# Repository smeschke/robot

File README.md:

Robot Platform 🛠️

Modular ESP32-based robot platform for outdoor navigation, motor control, and sensor integration.

This is a human-scale, differential-drive utility robot designed to move comfortably through real-world, ADA-compliant spaces at walking speed.

I chose 10-inch pneumatic tires so the robot can handle sidewalks, ramps, and grass reliably without suspension. The motors, gearboxes, and battery come from ride-on toys—they're inexpensive, readily available, and deliver excellent torque at low speeds.

The robot is controlled by an ESP32. The ESP32 uses ESPNOW to communicate with a manual joystick, or a computer. This allows the user to switch from 'auto' to 'manual' without touching any cords.

🔧 Technical Snapshot

The robot uses 550-type brushed DC motors with 100:1 reduction gearboxes driving 10-inch pneumatic wheels. It's powered by 12-volt, 7 amp-hour sealed lead-acid battery(s). Motor control is handled by BTS7960 H-bridge motor drivers.

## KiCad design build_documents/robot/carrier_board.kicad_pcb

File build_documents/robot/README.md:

# The Robot 🤖

Human-scale differential-drive utility robot built from ride-on toy parts: 550-type brushed motors with 100:1 gearboxes on 10-inch pneumatic wheels, powered by 12 V 7 Ah sealed lead-acid, driven by BTS7960 H-bridges. Ride-on toy drivetrains are cheap, everywhere, and geared for exactly this job — high torque at walking speed. The pneumatic tires handle sidewalks, ramps, and grass without any suspension, and it'll tow a cart.

## Architecture

There's no single robot brain — it's two independent ESP32s, each listening on ESP-NOW:

- **Motor board** ([`firmware/skidsteer_espnow.ino`](../../firmware/skidsteer_espnow.ino)) — receives the drive stream, does the skid-steer mixing, runs four BTS7960 channels.
- **Relay board** ([`firmware/relay_receiver.ino`](../../firmware/relay_receiver.ino)) — receives light events, drives two relays (left/right lights) for latched headlights and 2-second momentary turn signals.

Receivers tell packets apart purely by length (12-byte drive, 5-byte light event), so both boards can share the airwaves without a header byte or any routing. Anything that speaks the protocol can drive it — the single stick, the dual stick, or a computer through a reflashed controller — and switching between manual and auto control never involves touching a cord.

## Drive behavior

The motor board turns the joystick stream into arcade-mixed skid steer (throttle ± turn), with two safety behaviors worth knowing:

- **Fail-safe stop.** If no drive packet arrives for 300 ms, targets go to zero. The controller streams every 5 ms, so this only trips when the link is actually gone.
- **Ramping.** Motor output moves toward the target 1 PWM count every 3 ms (~0 to full in 0.75 s), so a stick flick doesn't dump full torque into the drivetrain — and the fail-safe stop is a controlled ramp-down, not a faceplant.

There's also a ~20% stick deadzone in the mixer, so the robot stays genuinely still at center.

## Lights

The relay board latches headlights on/off and fires momentary turn signals, deduping the controller's burst-resends by sequence number. A turn signal on one side never touches the other side's relay, and when it expires the relay reverts to the headlight state. Every ~500 ms it sends a heartbeat back (RSSI, relay state, uptime) — that's what feeds the dual stick controller's HUD. Controllers are auto-registered: first packet heard from a MAC becomes the peer, no pairing step.

## Build docs

- [Bill of materials](robot_bom.pdf)
- [Wiring diagram](robot_wiring_diagram.png)
- [Protocol details](robot_protocol.pdf)
- [STL files](stl_for_robot.md)

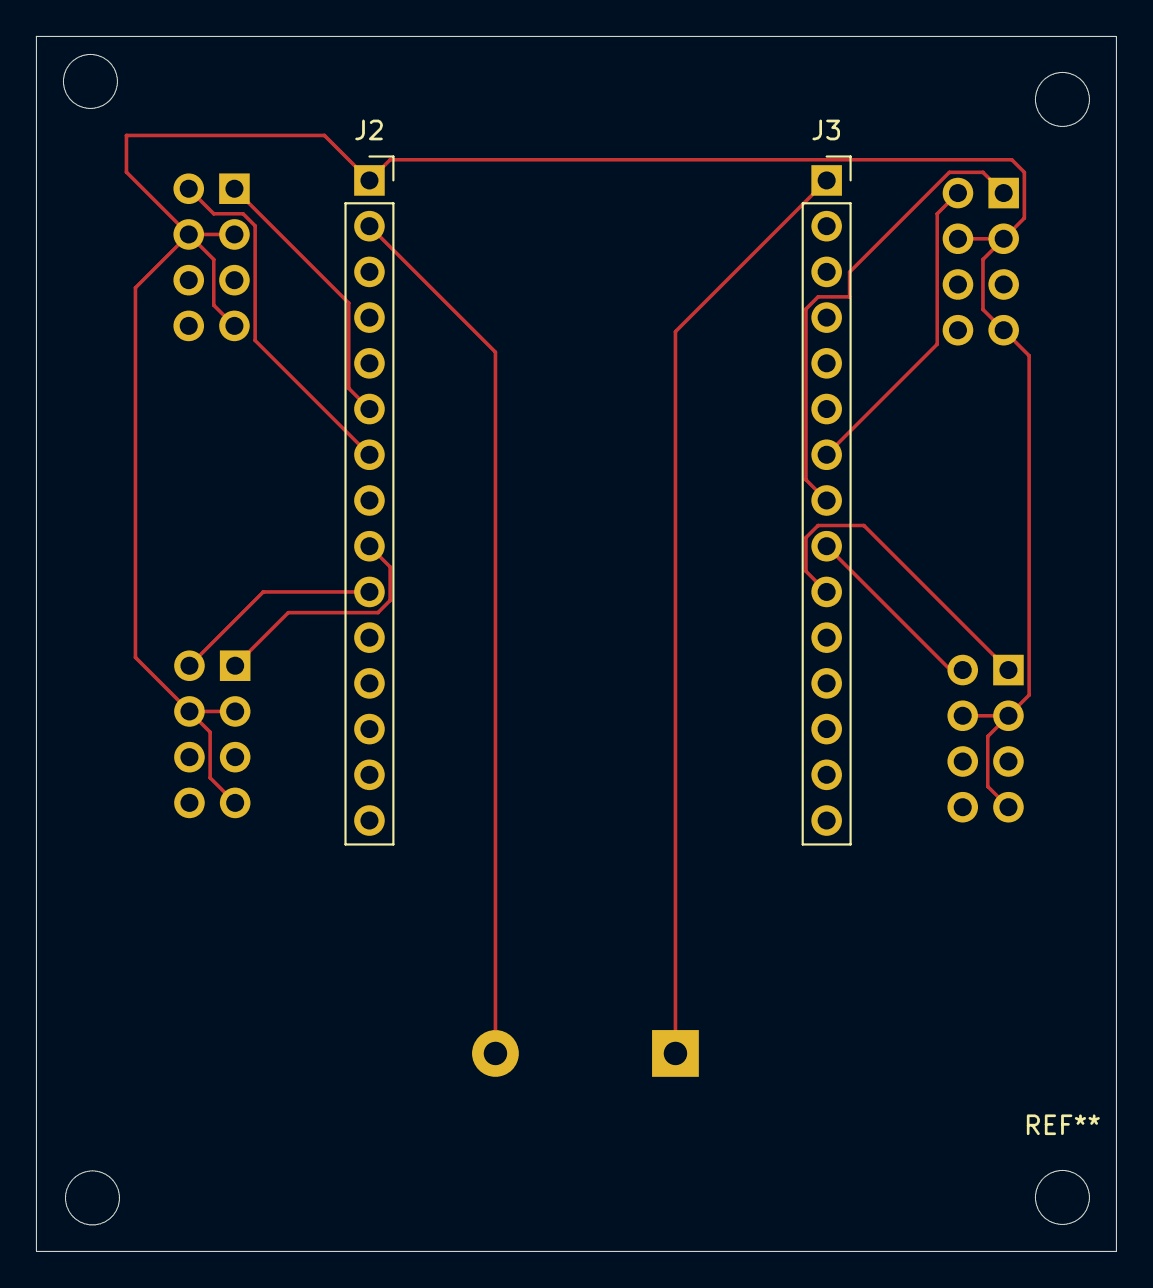
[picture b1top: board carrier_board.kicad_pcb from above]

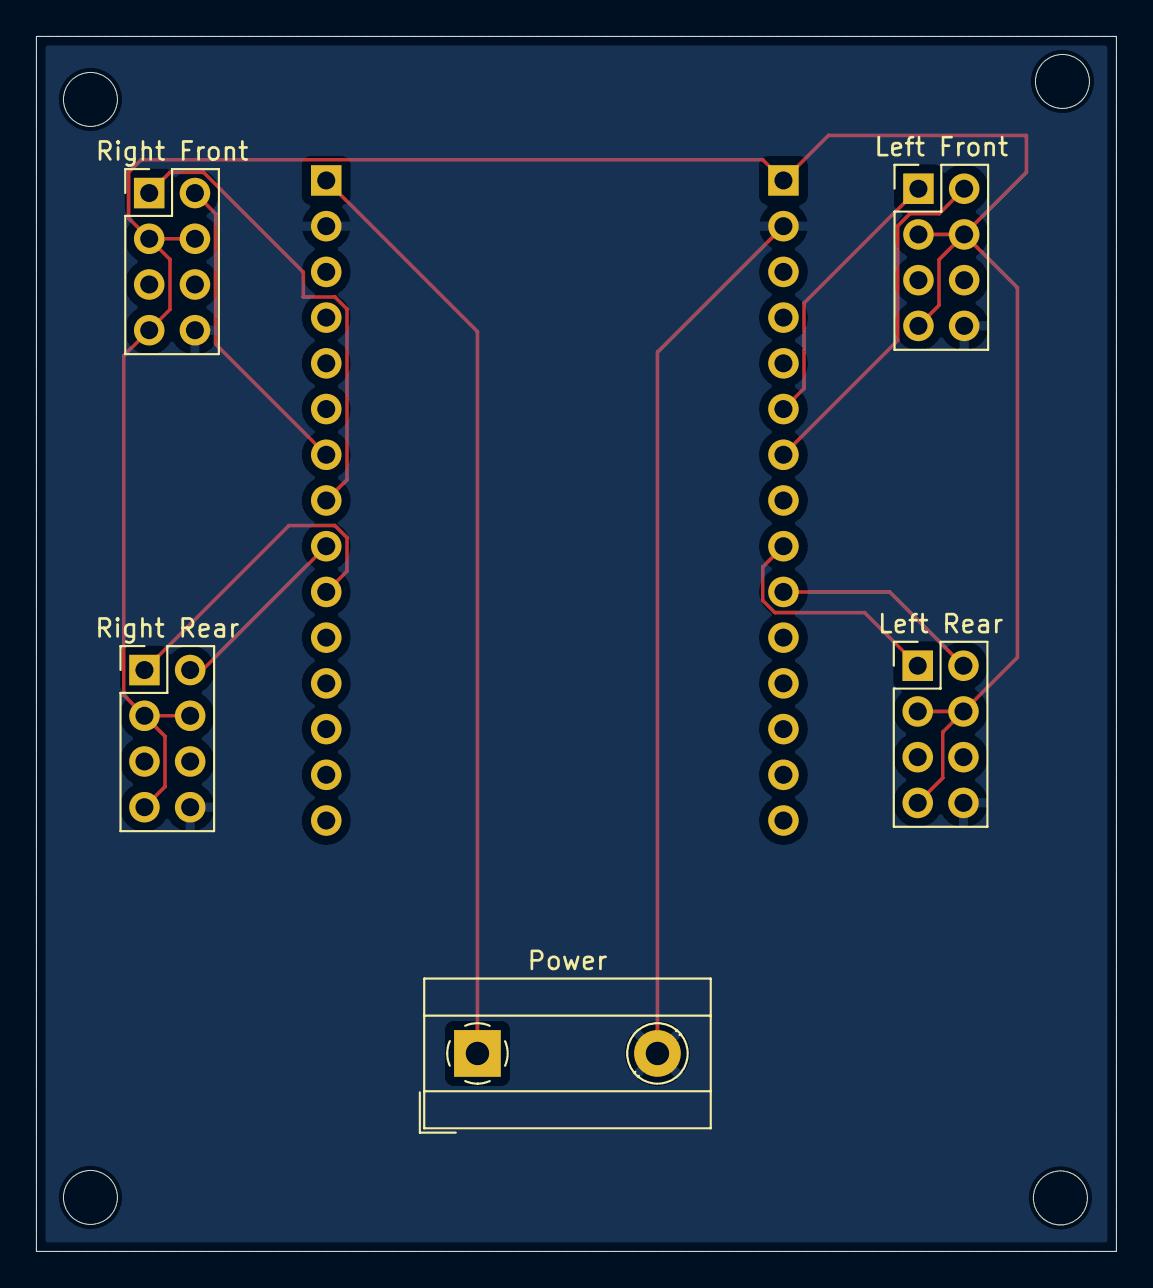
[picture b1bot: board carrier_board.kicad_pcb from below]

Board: 2 copper layers, 60.0 x 67.5 mm, 7 parts (5 on the bottom side), 11 nets.

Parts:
J2, J3: Conn_01x15; PinSocket_1x15_P2.54mm_Vertical
Left Front: Conn_02x04_Odd_Even; PinHeader_2x04_P2.54mm_Vertical
Left Rear: Conn_02x04_Odd_Even; PinHeader_2x04_P2.54mm_Vertical
Power: Screw_Terminal_01x02; TerminalBlock_MetzConnect_Type067_RT01902HDWC_1x02_P10.00mm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
Right Front: Conn_02x04_Odd_Even; PinHeader_2x04_P2.54mm_Vertical
Right Rear: Conn_02x04_Odd_Even; PinHeader_2x04_P2.54mm_Vertical

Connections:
/+3V3: J2.1, Left Front.3, Left Front.4, Left Front.7, Left Rear.3, Left Rear.4, Left Rear.7, Right Front.3, Right Front.4, Right Front.7, Right Rear.3, Right Rear.4, Right Rear.7
/+5V: J3.1, Power.1
/GND: J2.2, J3.2, Left Front.8, Left Rear.8, Power.2, Right Front.8, Right Rear.8
/GPIO16: J2.6, Left Front.1
/GPIO17: J2.7, Left Front.2
/GPIO18: J2.9, Left Rear.1
/GPIO19: J2.10, Left Rear.2
/GPIO25: J3.8, Right Front.1
/GPIO26: J3.7, Right Front.2
/GPIO32: J3.10, Right Rear.1
/GPIO33: J3.9, Right Rear.2

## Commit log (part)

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2026-01-26 Update r5d2_serial_control.ino
    added estop logic
2026-03-19 Add r5d2_hotspot_interface.ino file
2026-03-19 Revise README for clarity on robot platform features
    Updated the README to clarify the robot's purpose and capabilities.
2026-03-20 Correct typos and improve formatting in README
    Fixed typos and formatting issues in the README.
2026-06-22 Add joystick sender with LED control and ESP-NOW
